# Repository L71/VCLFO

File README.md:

VCLFO
=====

This is an LFO/oscillator with voltage control (uses LED+LDR circuit for F control).
Built-in attenuverter for frequency CV input. Outputs for triangle/saw + square wave. Three frequency ranges, sloooow to mid audio range.

Version 2 works better, it has exponential frequency response (don't expect it to be linear or precise, though!) and the LED will work corectly when in ramp output mode. 
The trimmer pot on the V. 2 can be used to tune the LFO rate ranges. The correct setting should be when it's at about 5-6 kOhm (the exponential converter output should just about reach the maximum negative voltage when the rate pot is at maximum). 

Panels and PCBs licensed cc-by-sa.

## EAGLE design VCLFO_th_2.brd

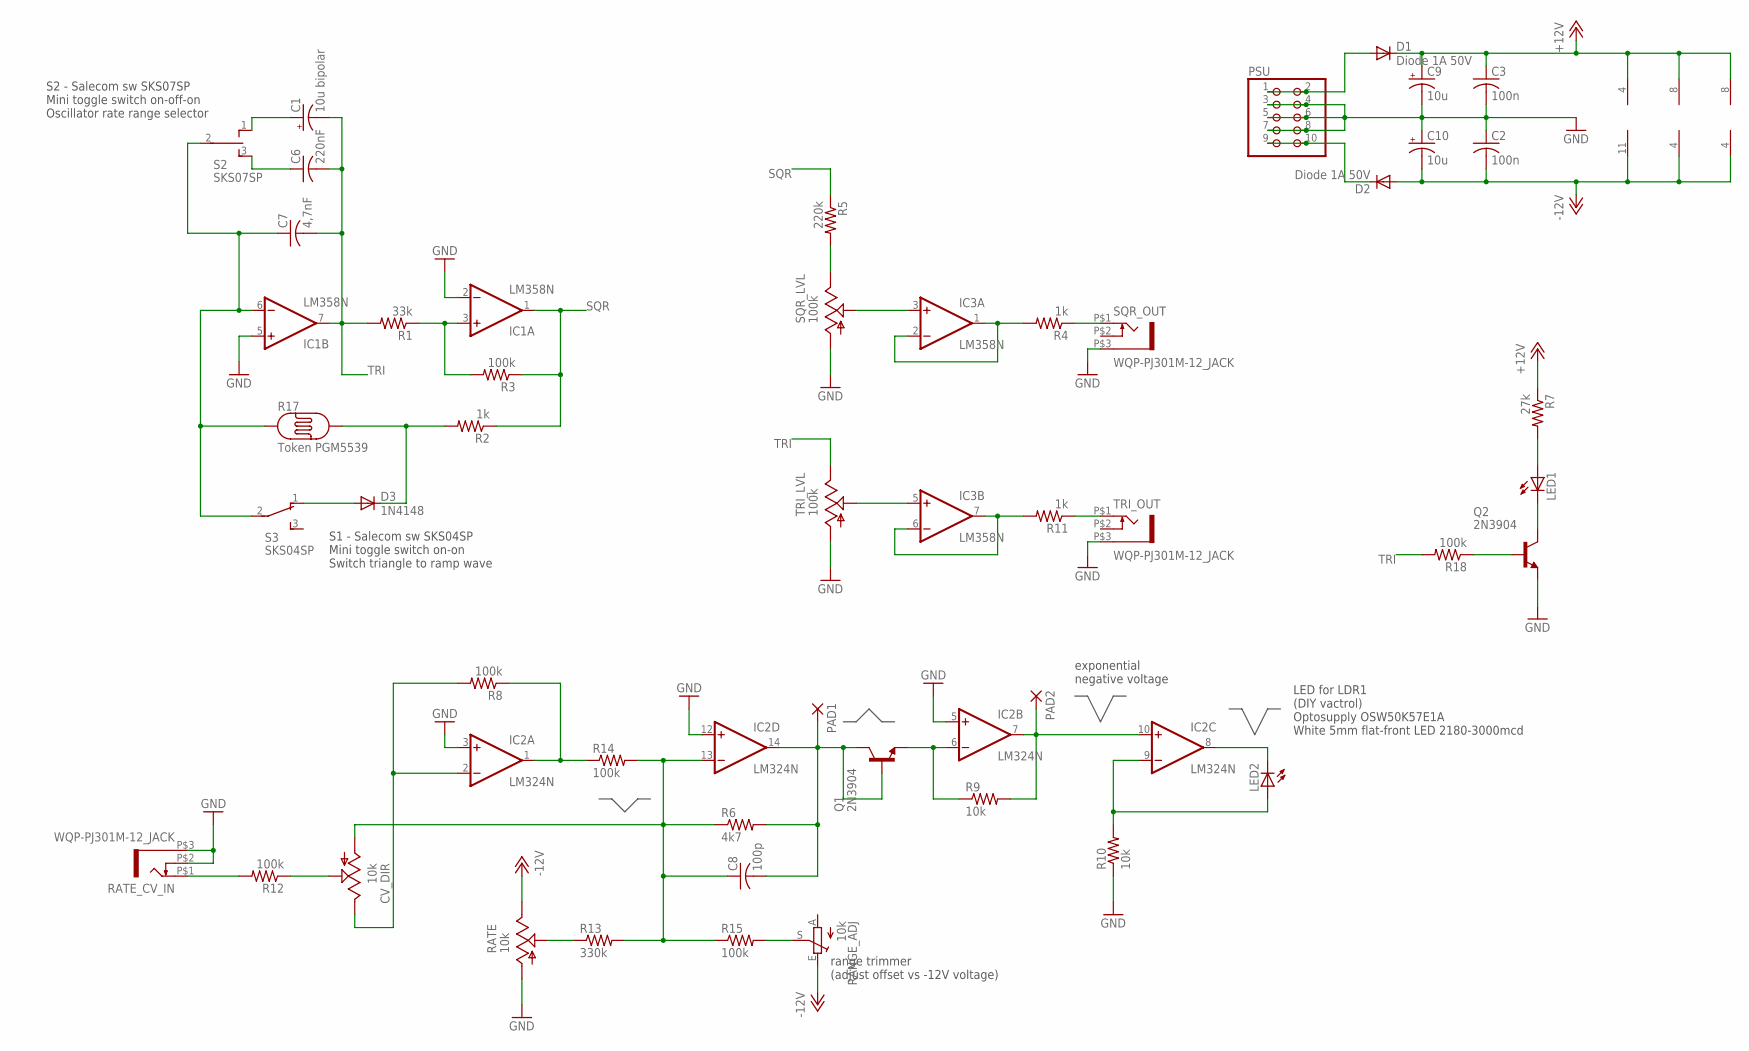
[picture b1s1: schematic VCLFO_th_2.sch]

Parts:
C1: 10u bipolar; E2,5-5
C2, C3: 100n; C025-025X050
C6: 220nF; C050-025X075
C7: 4,7nF; C025-025X050
C8: 100p; C025-025X050
C9, C10: 10u; E2,5-5
CV_DIR: 10k; ALPS_POT_VERTICAL
D1, D2: Diode 1A 50V; D-2.5
D3: 1N4148; D-5
IC1, IC3: LM358N; DIL08
IC2: LM324N; DIL14
LED1, LED2: LED5MM
PAD1, PAD2: 1,6/0,8
PSU: PINHD-2X5; 2X05
Q1, Q2: 2N3904; TO92
R1: 33k; 0204V
R2, R4, R11: 1k; 0204V
R3, R8, R12, R14, R15, R18: 100k; 0204V
R5: 220k; 0204V
R6: 4k7; 0204V
R7: 27k; 0204V
R9, R10: 10k; 0204V
R13: 330k; 0204V
R17: Token PGM5539; PHOTOCELL
RANGE_ADJ: 10k; B25P
RATE: 10k; ALPS_POT_VERTICAL
RATE_CV_IN: WQP-PJ301M-12_JACK
S2: SKS07SP; TL3XPO
S3: SKS04SP; TL3XPO
SQR_LVL: 100k; ALPS_POT_VERTICAL
SQR_OUT: WQP-PJ301M-12_JACK
TRI_LVL: 100k; ALPS_POT_VERTICAL
TRI_OUT: WQP-PJ301M-12_JACK

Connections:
+12V: C3.1, C9.+, D1.C, IC1.8 (V+), IC2.4 (V+), IC3.8 (V+), R7.1
-12V: C2.2, C10.-, D2.A, IC1.4 (V-), IC2.11 (V-), IC3.4 (V-), RANGE_ADJ.E, RATE.P$1 (E)
GND: C2.1, C3.2, C9.-, C10.+, IC1.2 (-IN), IC1.5 (+IN), IC2.3 (+IN), IC2.5 (+IN), IC2.12 (+IN), PSU.3, PSU.4, PSU.5, PSU.6, PSU.7, PSU.8, Q2.3 (E), R10.1, RATE.P$3 (A), RATE_CV_IN.P$2 (3), RATE_CV_IN.P$3 (1), SQR_LVL.P$3 (A), SQR_OUT.P$3 (1), TRI_LVL.P$3 (A), TRI_OUT.P$3 (1)
unnamed: C7.1, IC1.6 (-IN), R17.1, S2.2, S3.2
unnamed: D3.C, R2.2, R17.2
unnamed: IC3.1 (OUT), IC3.2 (-IN), R4.2
unnamed: R5.2, SQR_LVL.P$1 (E)
unnamed: IC1.3 (+IN), R1.1, R3.2
unnamed: R4.1, SQR_OUT.P$1 (2)
unnamed: CV_DIR.P$1 (E), IC2.2 (-IN), R8.2
unnamed: IC3.6 (-IN), IC3.7 (OUT), R11.2
unnamed: IC3.3 (+IN), SQR_LVL.P$2 (S)
unnamed: D1.A, PSU.1, PSU.2
unnamed: D2.C, PSU.9, PSU.10
unnamed: R12.2, RATE_CV_IN.P$1 (2)
unnamed: C8.2, IC2.14 (OUT), PAD1.1, Q1.1 (C), Q1.2 (B), R6.2
unnamed: C1.+, S2.1 (O)
unnamed: CV_DIR.P$2 (S), R12.1
unnamed: D3.A, S3.1 (O)
unnamed: R11.1, TRI_OUT.P$1 (2)
unnamed: R13.1, RATE.P$2 (S)
unnamed: C6.1, S2.3 (S)
unnamed: Q2.2 (B), R18.1
unnamed: IC2.6 (-IN), Q1.3 (E), R9.1
unnamed: IC2.1 (OUT), R8.1, R14.1
unnamed: C8.1, CV_DIR.P$3 (A), IC2.13 (-IN), R6.1, R13.2, R14.2, R15.1
unnamed: IC2.7 (OUT), IC2.10 (+IN), PAD2.1, R9.2
unnamed: R15.2, RANGE_ADJ.S
unnamed: IC2.8 (OUT), LED2.K (C)
unnamed: IC2.9 (-IN), LED2.A, R10.2
unnamed: IC3.5 (+IN), TRI_LVL.P$2 (S)
unnamed: LED1.K (C), Q2.1 (C)
unnamed: LED1.A, R7.2
SQR: IC1.1 (OUT), R2.1, R3.1, R5.1
TRI: C1.-, C6.2, C7.2, IC1.7 (OUT), R1.2, R18.2, TRI_LVL.P$1 (E)

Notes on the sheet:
S1 - Salecom sw SKS04SP Mini toggle switch on-on Switch triangle to ramp wave
LED for LDR1 (DIY vactrol) Optosupply OSW50K57E1A White 5mm flat-front LED 2180-3000mcd
S2 - Salecom sw SKS07SP Mini toggle switch on-off-on Oscillator rate range selector
range trimmer (adjust offset vs -12V voltage)
exponential negative voltage

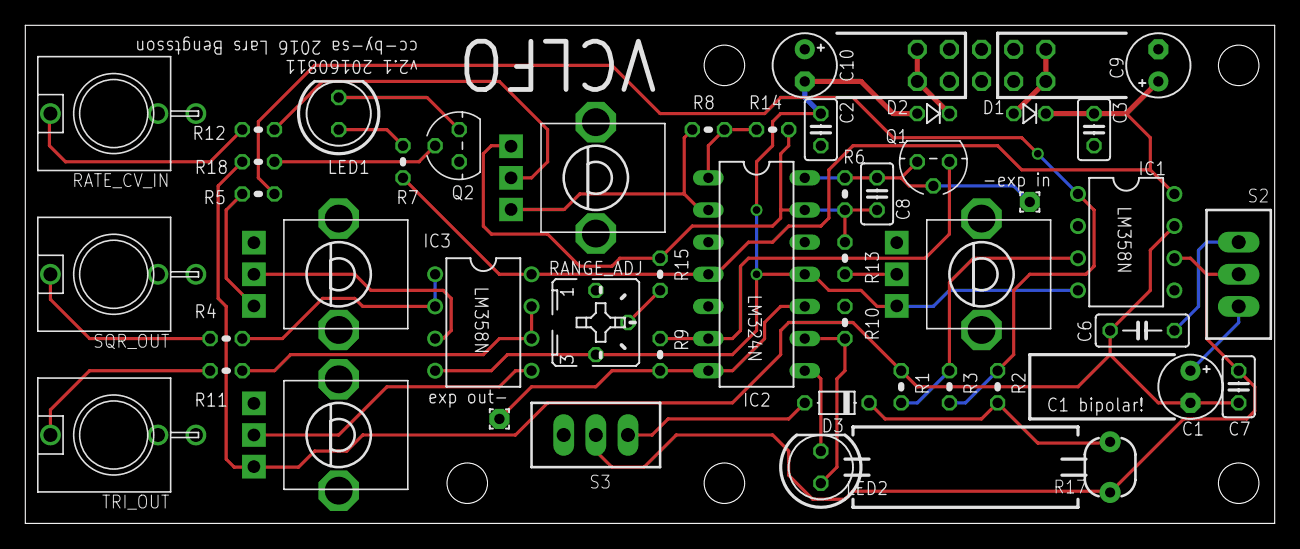
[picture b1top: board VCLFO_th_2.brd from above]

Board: 2 copper layers, 98.7 x 39.4 mm, 48 parts (1 on the bottom side), 35 nets.

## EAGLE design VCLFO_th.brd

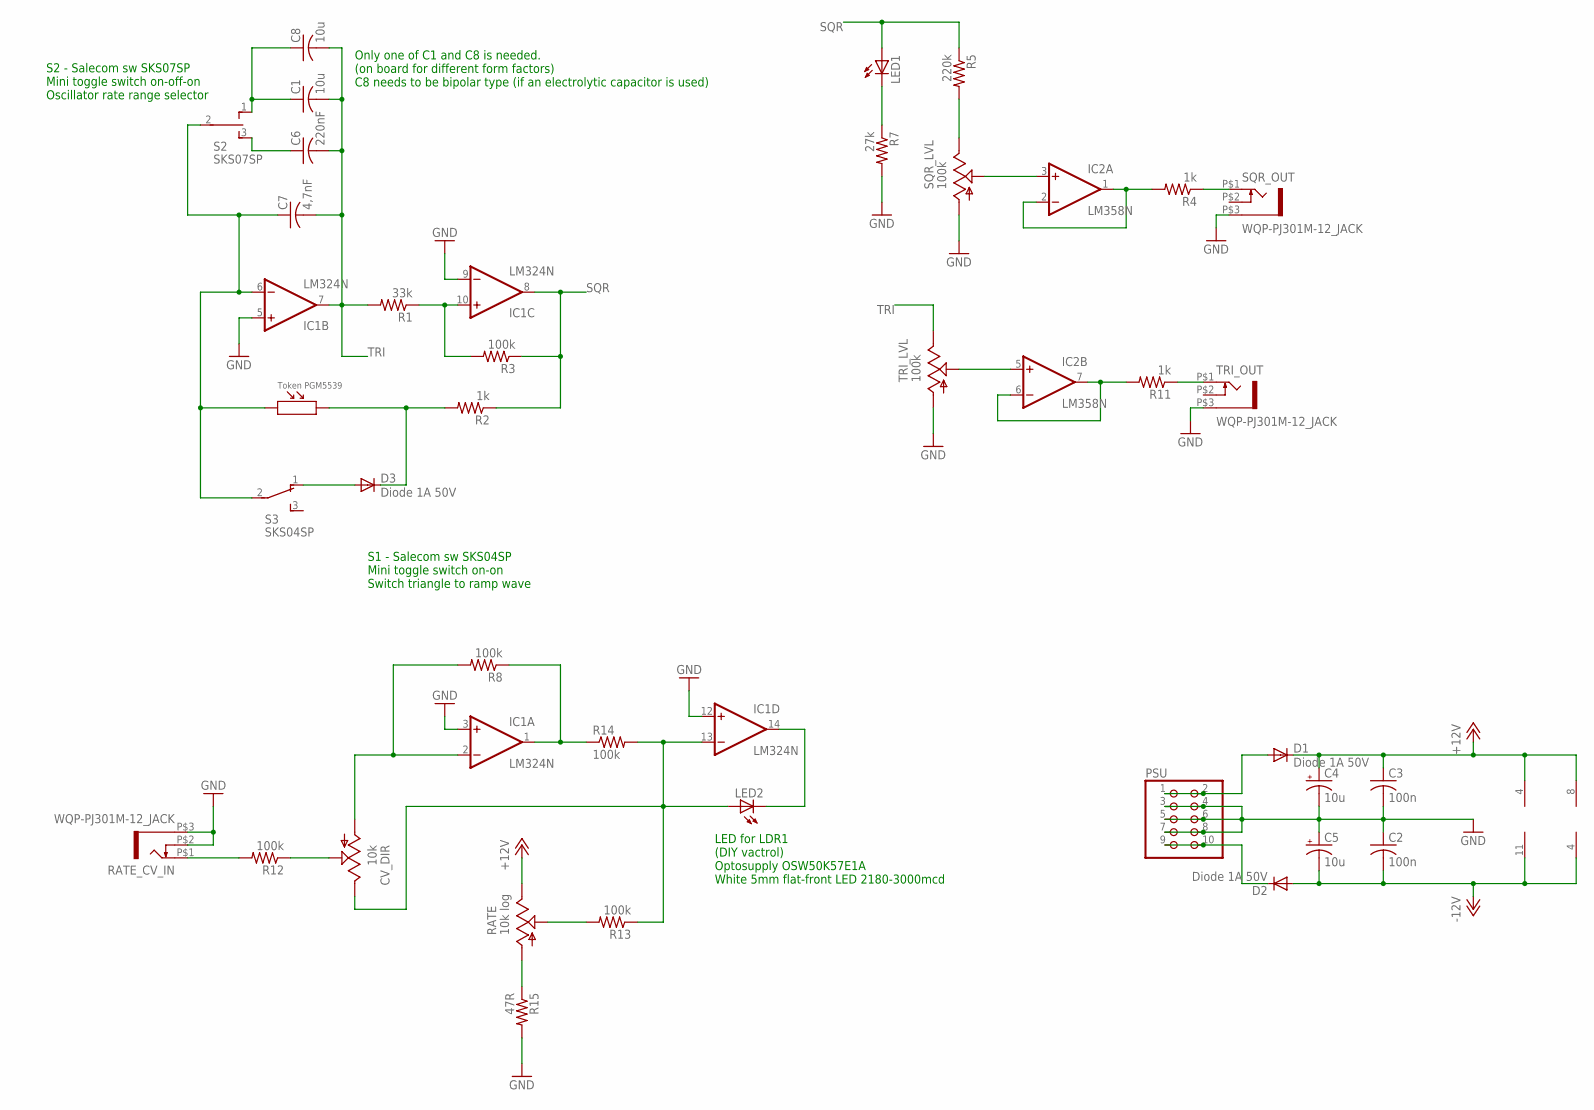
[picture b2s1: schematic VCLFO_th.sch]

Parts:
C1: 10u; C1206
C2, C3: 100n; C025-025X050
C4, C5: 10u; E2,5-6
C6: 220nF; C025-025X050
C7: 4,7nF; C025-025X050
C8: 10u; C025-050X050
CV_DIR: 10k; ALPS_POT_VERTICAL
D1, D2, D3: Diode 1A 50V; D-5
IC1: LM324N; DIL14
IC2: LM358N; DIL08
LDR1: Token PGM5539; LDR_SNR2-3.0
LED1: LED5MM
LED2: LED3MM
PSU: PINHD-2X5; 2X05
R1: 33k; 0207/2V
R2, R4, R11: 1k; 0207/2V
R3, R8, R12, R13, R14: 100k; 0207/2V
R5: 220k; 0207/2V
R7: 27k; 0207/2V
R15: 47R; 0207/2V
RATE: 10k log; ALPS_POT_VERTICAL
RATE_CV_IN: WQP-PJ301M-12_JACK
S2: SKS07SP; TL3XPO
S3: SKS04SP; TL3XPO
SQR_LVL: 100k; ALPS_POT_VERTICAL
SQR_OUT: WQP-PJ301M-12_JACK
TRI_LVL: 100k; ALPS_POT_VERTICAL
TRI_OUT: WQP-PJ301M-12_JACK

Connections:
+12V: C3.1, C4.+, D1.C, IC1.4 (V+), IC2.8 (V+), RATE.P$1 (E)
-12V: C2.2, C5.-, D2.A, IC1.11 (V-), IC2.4 (V-)
GND: C2.1, C3.2, C4.-, C5.+, IC1.3 (+IN), IC1.5 (+IN), IC1.9 (-IN), IC1.12 (+IN), PSU.3, PSU.4, PSU.5, PSU.6, PSU.7, PSU.8, R7.2, R15.2, RATE_CV_IN.P$2 (3), RATE_CV_IN.P$3 (1), SQR_LVL.P$3 (A), SQR_OUT.P$3 (1), TRI_LVL.P$3 (A), TRI_OUT.P$3 (1)
unnamed: C7.1, IC1.6 (-IN), LDR1.1, S2.2, S3.2
unnamed: LED1.K (C), R7.1
unnamed: IC2.1 (OUT), IC2.2 (-IN), R4.2
unnamed: R5.2, SQR_LVL.P$1 (E)
unnamed: IC1.10 (+IN), R1.1, R3.2
unnamed: R4.1, SQR_OUT.P$1 (2)
unnamed: D3.C, LDR1.2, R2.2
unnamed: IC2.6 (-IN), IC2.7 (OUT), R11.2
unnamed: IC2.3 (+IN), SQR_LVL.P$2 (S)
unnamed: D1.A, PSU.1, PSU.2
unnamed: D2.C, PSU.9, PSU.10
unnamed: R12.2, RATE_CV_IN.P$1 (2)
unnamed: C1.1, C8.1, S2.1 (O)
unnamed: CV_DIR.P$2 (S), R12.1
unnamed: D3.A, S3.1 (O)
unnamed: R11.1, TRI_OUT.P$1 (2)
unnamed: C6.1, S2.3 (S)
unnamed: CV_DIR.P$3 (A), IC1.2 (-IN), R8.2
unnamed: IC1.14 (OUT), LED2.K (C)
unnamed: IC1.1 (OUT), R8.1, R14.1
unnamed: CV_DIR.P$1 (E), IC1.13 (-IN), LED2.A, R13.1, R14.2
unnamed: R13.2, RATE.P$2 (S)
unnamed: R15.1, RATE.P$3 (A)
unnamed: IC2.5 (+IN), TRI_LVL.P$2 (S)
SQR: IC1.8 (OUT), LED1.A, R2.1, R3.1, R5.1
TRI: C1.2, C6.2, C7.2, C8.2, IC1.7 (OUT), R1.2, TRI_LVL.P$1 (E)

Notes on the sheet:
S1 - Salecom sw SKS04SP Mini toggle switch on-on Switch triangle to ramp wave
LED for LDR1 (DIY vactrol) Optosupply OSW50K57E1A White 5mm flat-front LED 2180-3000mcd
S2 - Salecom sw SKS07SP Mini toggle switch on-off-on Oscillator rate range selector
Only one of C1 and C8 is needed. (on board for different form factors) C8 needs to be bipolar type (if an electrolytic capacitor is used)

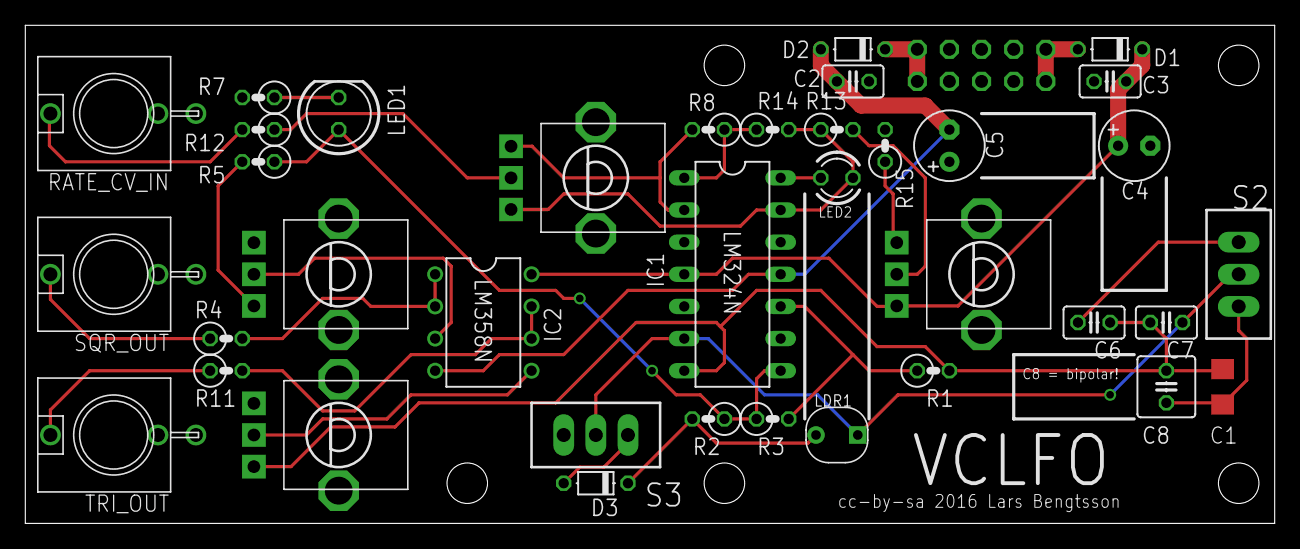
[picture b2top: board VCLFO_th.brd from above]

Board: 2 copper layers, 98.7 x 39.4 mm, 38 parts (1 on the bottom side), 29 nets.

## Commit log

2016-03-28 Initial upload.
2016-03-28 Updated component values of LED2 and LDR1 (Vactrol/optocoupler).
2016-03-29 Added comment about C1/C8.
2016-04-06 Added panel.
2016-04-06 Added readme.
2016-04-17 Renamed IC3->IC2. Rate CV potentiometer was 1/40" off, corrected. Moved IC1 1/40" towards same pot, makes a bit more space for optical stuff. Moved R15 a bit, moved C6 and C7.
2016-04-17 Minor updates to labels.
2016-05-16 Initial add, version with exponential converter for rate control voltage.
2016-05-18 Added info about V2 of module.
2016-08-11 Fixed circuit around timer vactrol (bypass diode for saw wave works better at high rates). Changed biggest timer cap + the bigger PSU caps from 1206 to TH electrolytics. Rerouted accordingly.
2016-10-17 Removed ledftover label on back of PCB. Changed footprint for vactrol LED to 5mm (easier to see polarity after manufacturing).
2017-08-26 Added PCB front panel. (not yet tested)

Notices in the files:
VCLFO_th.brd:
cc-by-sa 2016 Lars Bengtsson
parts and their libraries:
SparkFun-Sensors: Licensing: Creative Commons ShareAlike 4.0 International - https://creativecommons.org/licenses/by-sa/4.0
